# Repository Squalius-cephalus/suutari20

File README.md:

## Suutari20

Suutari20 is a RP2040 based modular macro keyboard. It uses TRRS sockets and supports 3.5mm jacks from TS to TRRS. Firmware uses QMK with Vial.

**Build guide and information about modules can be found here: https://github.com/Squalius-cephalus/suutari20/wiki/Getting-started**

**Bill of materials - Suutari20**
- 3D printed case
- PCB
- 4x M2xL3xOD3 heatset inserts 
- 4x M2 bolts
- 8x PJ-320A audio sockets
- Raspberry Pi Pico or pin compatible clone

For now most of the information about Suutari20 can be found on this video:

TODO:
- Add images
- Add more info about modules

PCB design uses footprints from [ScottoKeebs](https://github.com/joe-scotto/scottokeebs/tree/main/Extras/ScottoKicad "ScottoKeebs") and [kbd library.](https://github.com/foostan/kbd "kbd library.")

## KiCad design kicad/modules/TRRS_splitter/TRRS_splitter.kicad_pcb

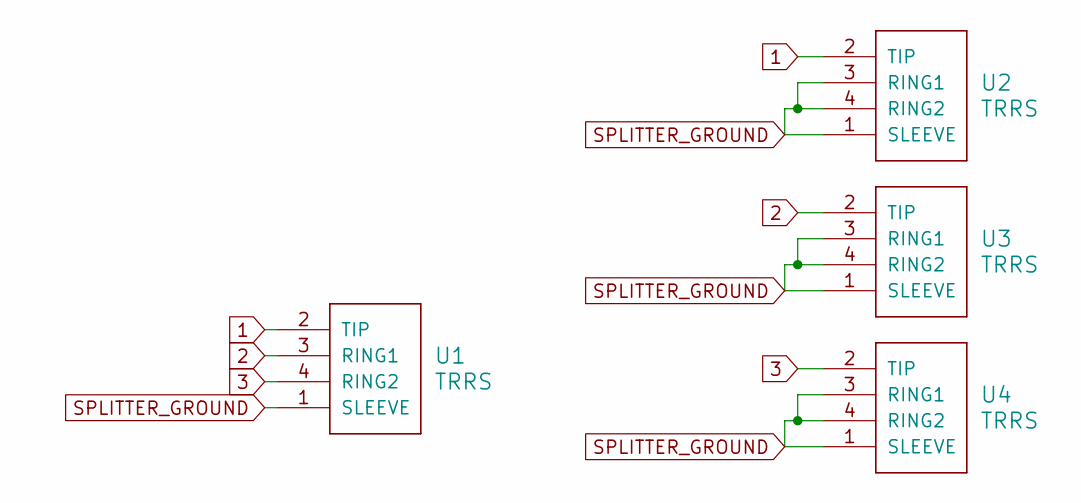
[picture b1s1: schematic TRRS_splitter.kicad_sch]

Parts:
U1, U2, U3, U4: TRRS; TRRS_PJ-320A

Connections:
1: U1.2 (TIP), U2.2 (TIP)
2: U1.3 (RING1), U3.2 (TIP)
3: U1.4 (RING2), U4.2 (TIP)
SPLITTER_GROUND: U1.1 (SLEEVE), U2.1 (SLEEVE), U2.3 (RING1), U2.4 (RING2), U3.1 (SLEEVE), U3.3 (RING1), U3.4 (RING2), U4.1 (SLEEVE), U4.3 (RING1), U4.4 (RING2)

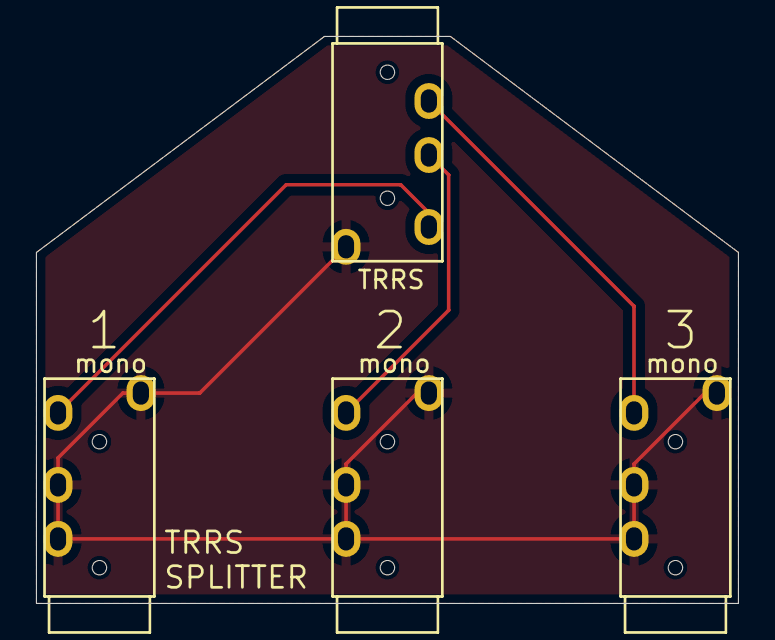
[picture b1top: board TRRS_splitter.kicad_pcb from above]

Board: 2 copper layers, 39.0 x 31.5 mm, 4 parts (0 on the bottom side), 4 nets.

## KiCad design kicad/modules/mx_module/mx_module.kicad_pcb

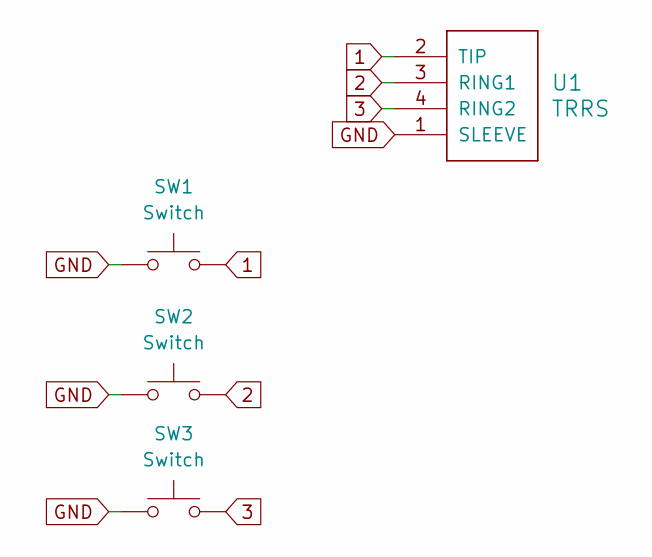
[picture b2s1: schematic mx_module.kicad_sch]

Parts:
SW1, SW2, SW3: Switch; CherryMX_MidHeight_Hotswap
U1: TRRS; TRRS_PJ-320A

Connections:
1: SW1.2, U1.2 (TIP)
2: SW2.2, U1.3 (RING1)
3: SW3.2, U1.4 (RING2)
GND: SW1.1, SW2.1, SW3.1, U1.1 (SLEEVE)

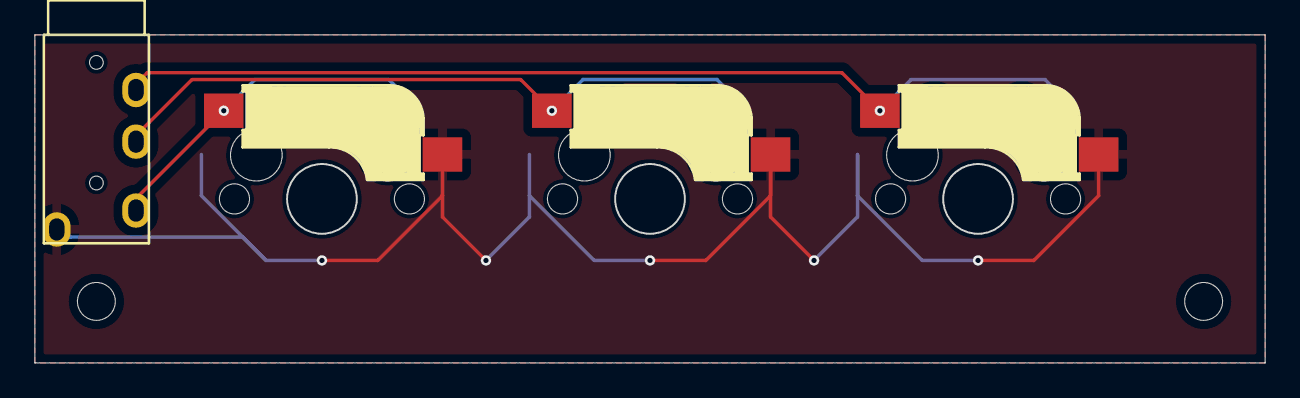
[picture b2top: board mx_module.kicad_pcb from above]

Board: 2 copper layers, 71.4 x 19.1 mm, 4 parts (0 on the bottom side), 4 nets.

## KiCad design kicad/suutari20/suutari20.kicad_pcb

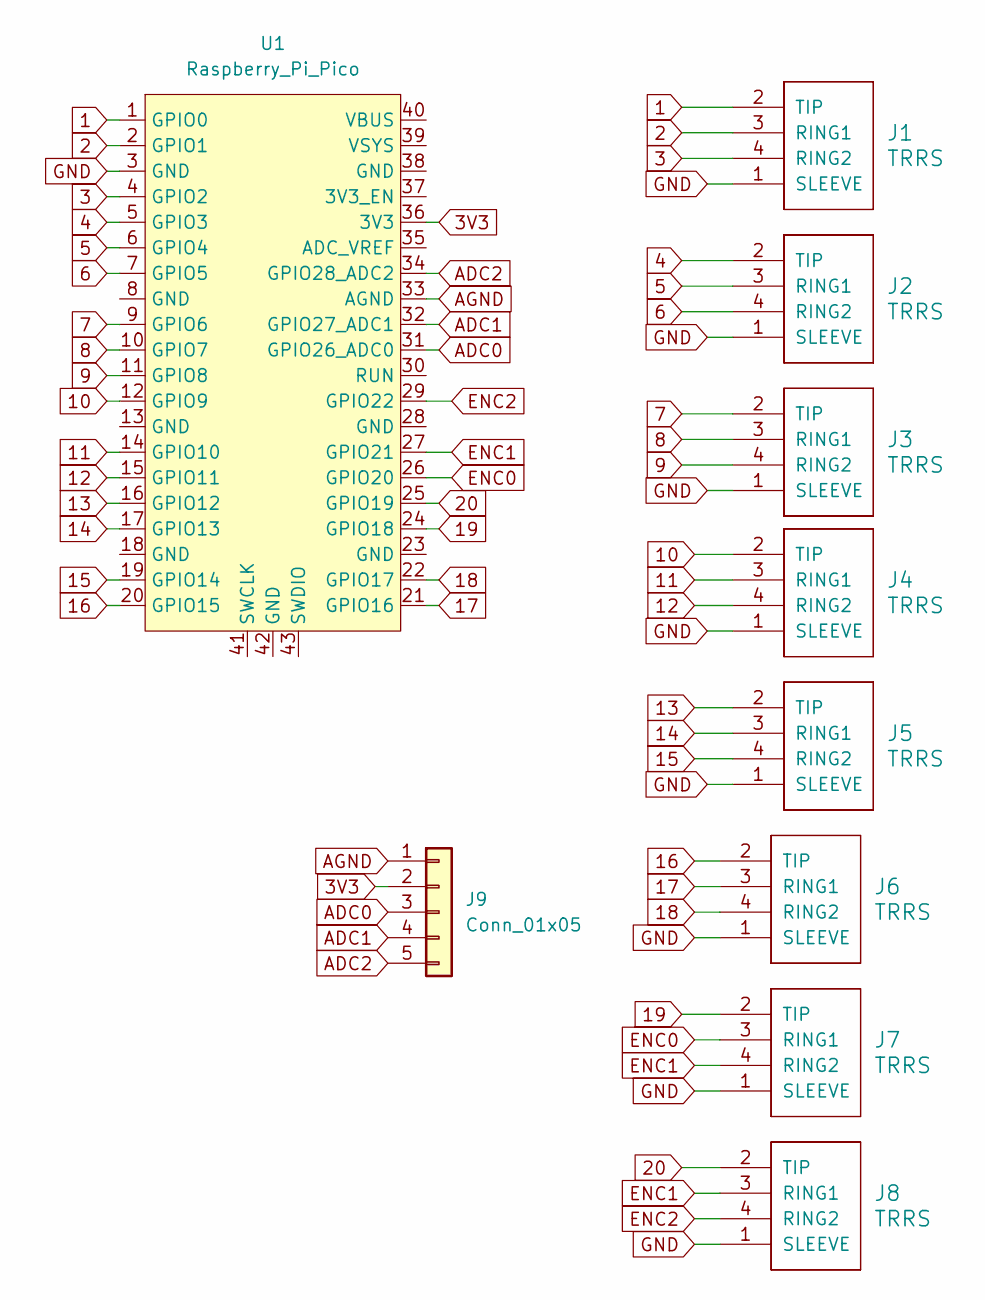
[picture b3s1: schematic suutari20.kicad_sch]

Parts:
J1, J2, J3, J4, J5, J6, J7, J8: TRRS; TRRS_PJ-320A
J9: Conn_01x05; JST_XH_B5B-XH-A_1x05_P2.50mm_Vertical
U1: Raspberry_Pi_Pico

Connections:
1: J1.2 (TIP), U1.1 (GPIO0)
2: J1.3 (RING1), U1.2 (GPIO1)
3: J1.4 (RING2), U1.4 (GPIO2)
3V3: J9.2, U1.36 (3V3)
4: J2.2 (TIP), U1.5 (GPIO3)
5: J2.3 (RING1), U1.6 (GPIO4)
6: J2.4 (RING2), U1.7 (GPIO5)
7: J3.2 (TIP), U1.9 (GPIO6)
8: J3.3 (RING1), U1.10 (GPIO7)
9: J3.4 (RING2), U1.11 (GPIO8)
10: J4.2 (TIP), U1.12 (GPIO9)
11: J4.3 (RING1), U1.14 (GPIO10)
12: J4.4 (RING2), U1.15 (GPIO11)
13: J5.2 (TIP), U1.16 (GPIO12)
14: J5.3 (RING1), U1.17 (GPIO13)
15: J5.4 (RING2), U1.19 (GPIO14)
16: J6.2 (TIP), U1.20 (GPIO15)
17: J6.3 (RING1), U1.21 (GPIO16)
18: J6.4 (RING2), U1.22 (GPIO17)
19: J7.2 (TIP), U1.24 (GPIO18)
20: J8.2 (TIP), U1.25 (GPIO19)
ADC0: J9.3, U1.31 (GPIO26_ADC0)
ADC1: J9.4, U1.32 (GPIO27_ADC1)
ADC2: J9.5, U1.34 (GPIO28_ADC2)
AGND: J9.1, U1.33 (AGND)
ENC0: J7.3 (RING1), U1.26 (GPIO20)
ENC1: J7.4 (RING2), J8.3 (RING1), U1.27 (GPIO21)
ENC2: J8.4 (RING2), U1.29 (GPIO22)
GND: J1.1 (SLEEVE), J2.1 (SLEEVE), J3.1 (SLEEVE), J4.1 (SLEEVE), J5.1 (SLEEVE), J6.1 (SLEEVE), J7.1 (SLEEVE), J8.1 (SLEEVE), U1.3 (GND)

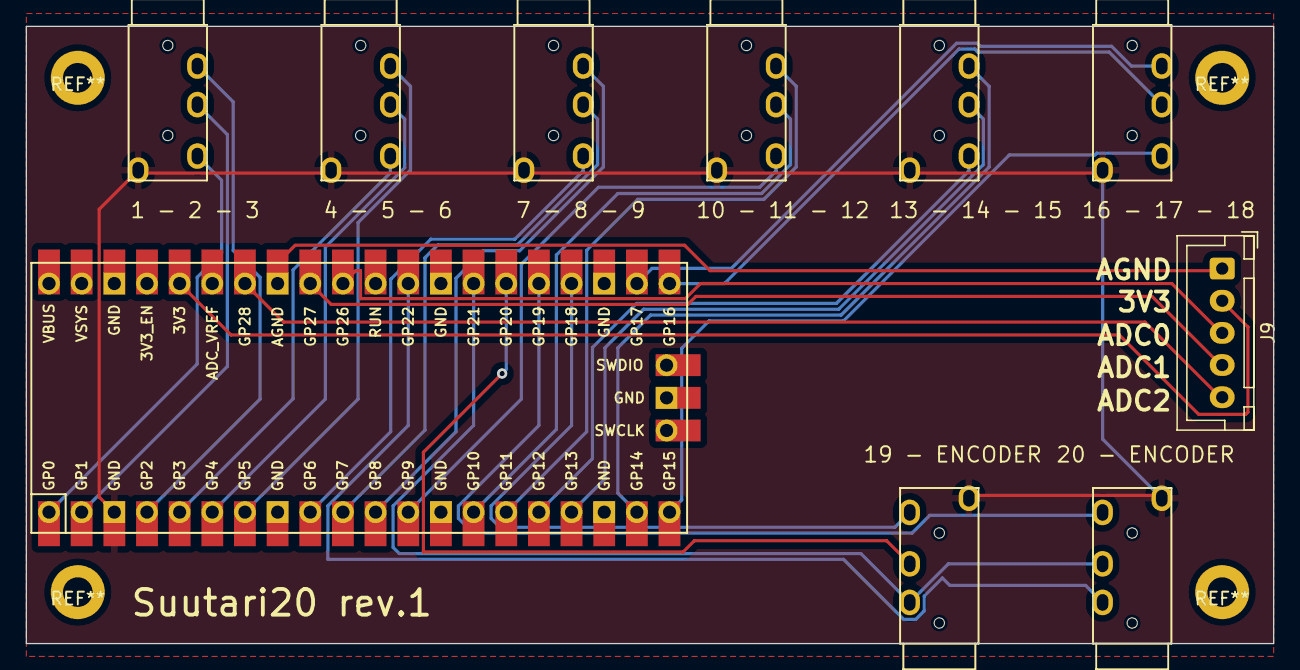
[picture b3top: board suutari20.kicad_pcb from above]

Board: 2 copper layers, 97.0 x 48.0 mm, 10 parts (0 on the bottom side), 29 nets.

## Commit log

2025-11-11 Added PCB files and gerber for the main module
2025-11-13 Added more info and enabled more functions on vial-qmk
2025-12-01 Added missing STL files and kicad files for the modules
2025-12-01 Create LICENSE
